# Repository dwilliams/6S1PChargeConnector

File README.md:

# 6S1PChargeConnector
A quick little board to make connecting 6 LiPo cells to a charger easier.

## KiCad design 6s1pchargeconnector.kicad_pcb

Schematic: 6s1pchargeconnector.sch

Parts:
P1: CHARGE; ECG.0B.307; Part Num 1124-1321-ND
P2: OUT; Pin_Header_Straight_1x02; Part Num PRT-10571
P3: BATT 6; JST-PH-2; Part Num PRT-08612
P4: BATT 5; JST-PH-2; Part Num PRT-08612
P5: BATT 4; JST-PH-2; Part Num PRT-08612
P6: BATT 3; JST-PH-2; Part Num PRT-08612
P7: BATT 2; JST-PH-2; Part Num PRT-08612
P8: BATT 1; JST-PH-2; Part Num PRT-08612

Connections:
unnamed: P1.1, P2.1, P8.3
unnamed: P1.2, P7.3, P8.2
unnamed: P1.3, P6.3, P7.2
unnamed: P1.4, P5.3, P6.2
unnamed: P1.5, P4.3, P5.2
unnamed: P1.6, P3.3, P4.2
unnamed: P1.7, P2.2, P3.2

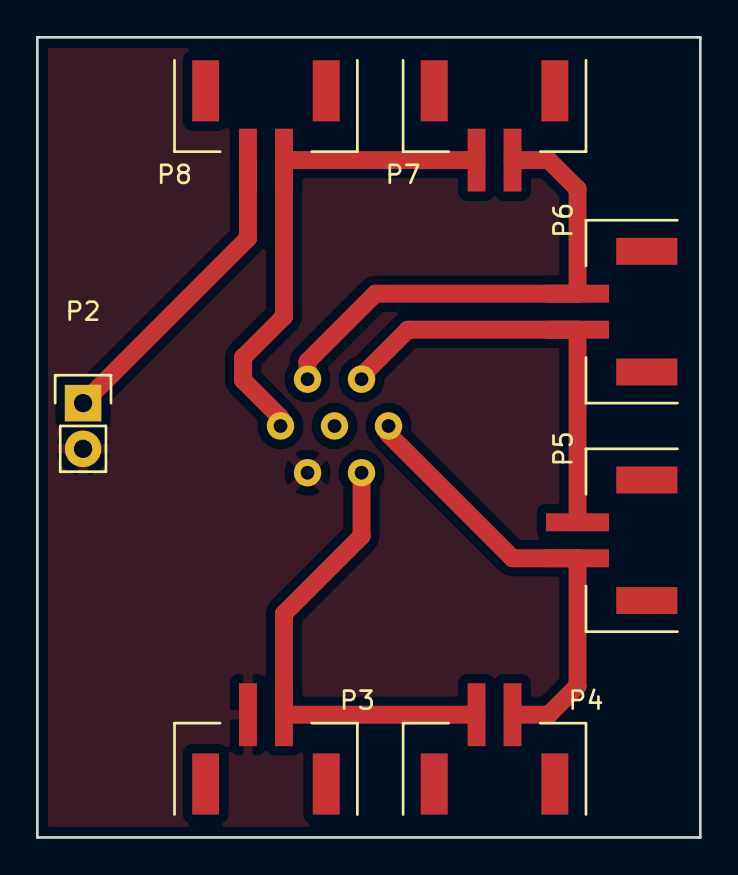
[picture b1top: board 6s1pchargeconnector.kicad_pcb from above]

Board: 2 copper layers, 36.8 x 44.4 mm, 8 parts (1 on the bottom side), 7 nets.

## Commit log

2015-10-16 Starting kicad project and adding schematic.
2015-10-16 Added a schematic symbol and footprint for the 2 pin JST-PH connector.
2015-10-18 Added the other two connectors, pcb, gerbers, and bom.
2015-10-21 Added a missing trace and updated the gerbers.
